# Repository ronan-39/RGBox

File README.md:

# RGBox
 Slim hitbox styled fighting game controller based on the RP2040 microcontroller. Laser cut acyrlic case with 3D printed keycaps for Kailh low profile mechanical switches.

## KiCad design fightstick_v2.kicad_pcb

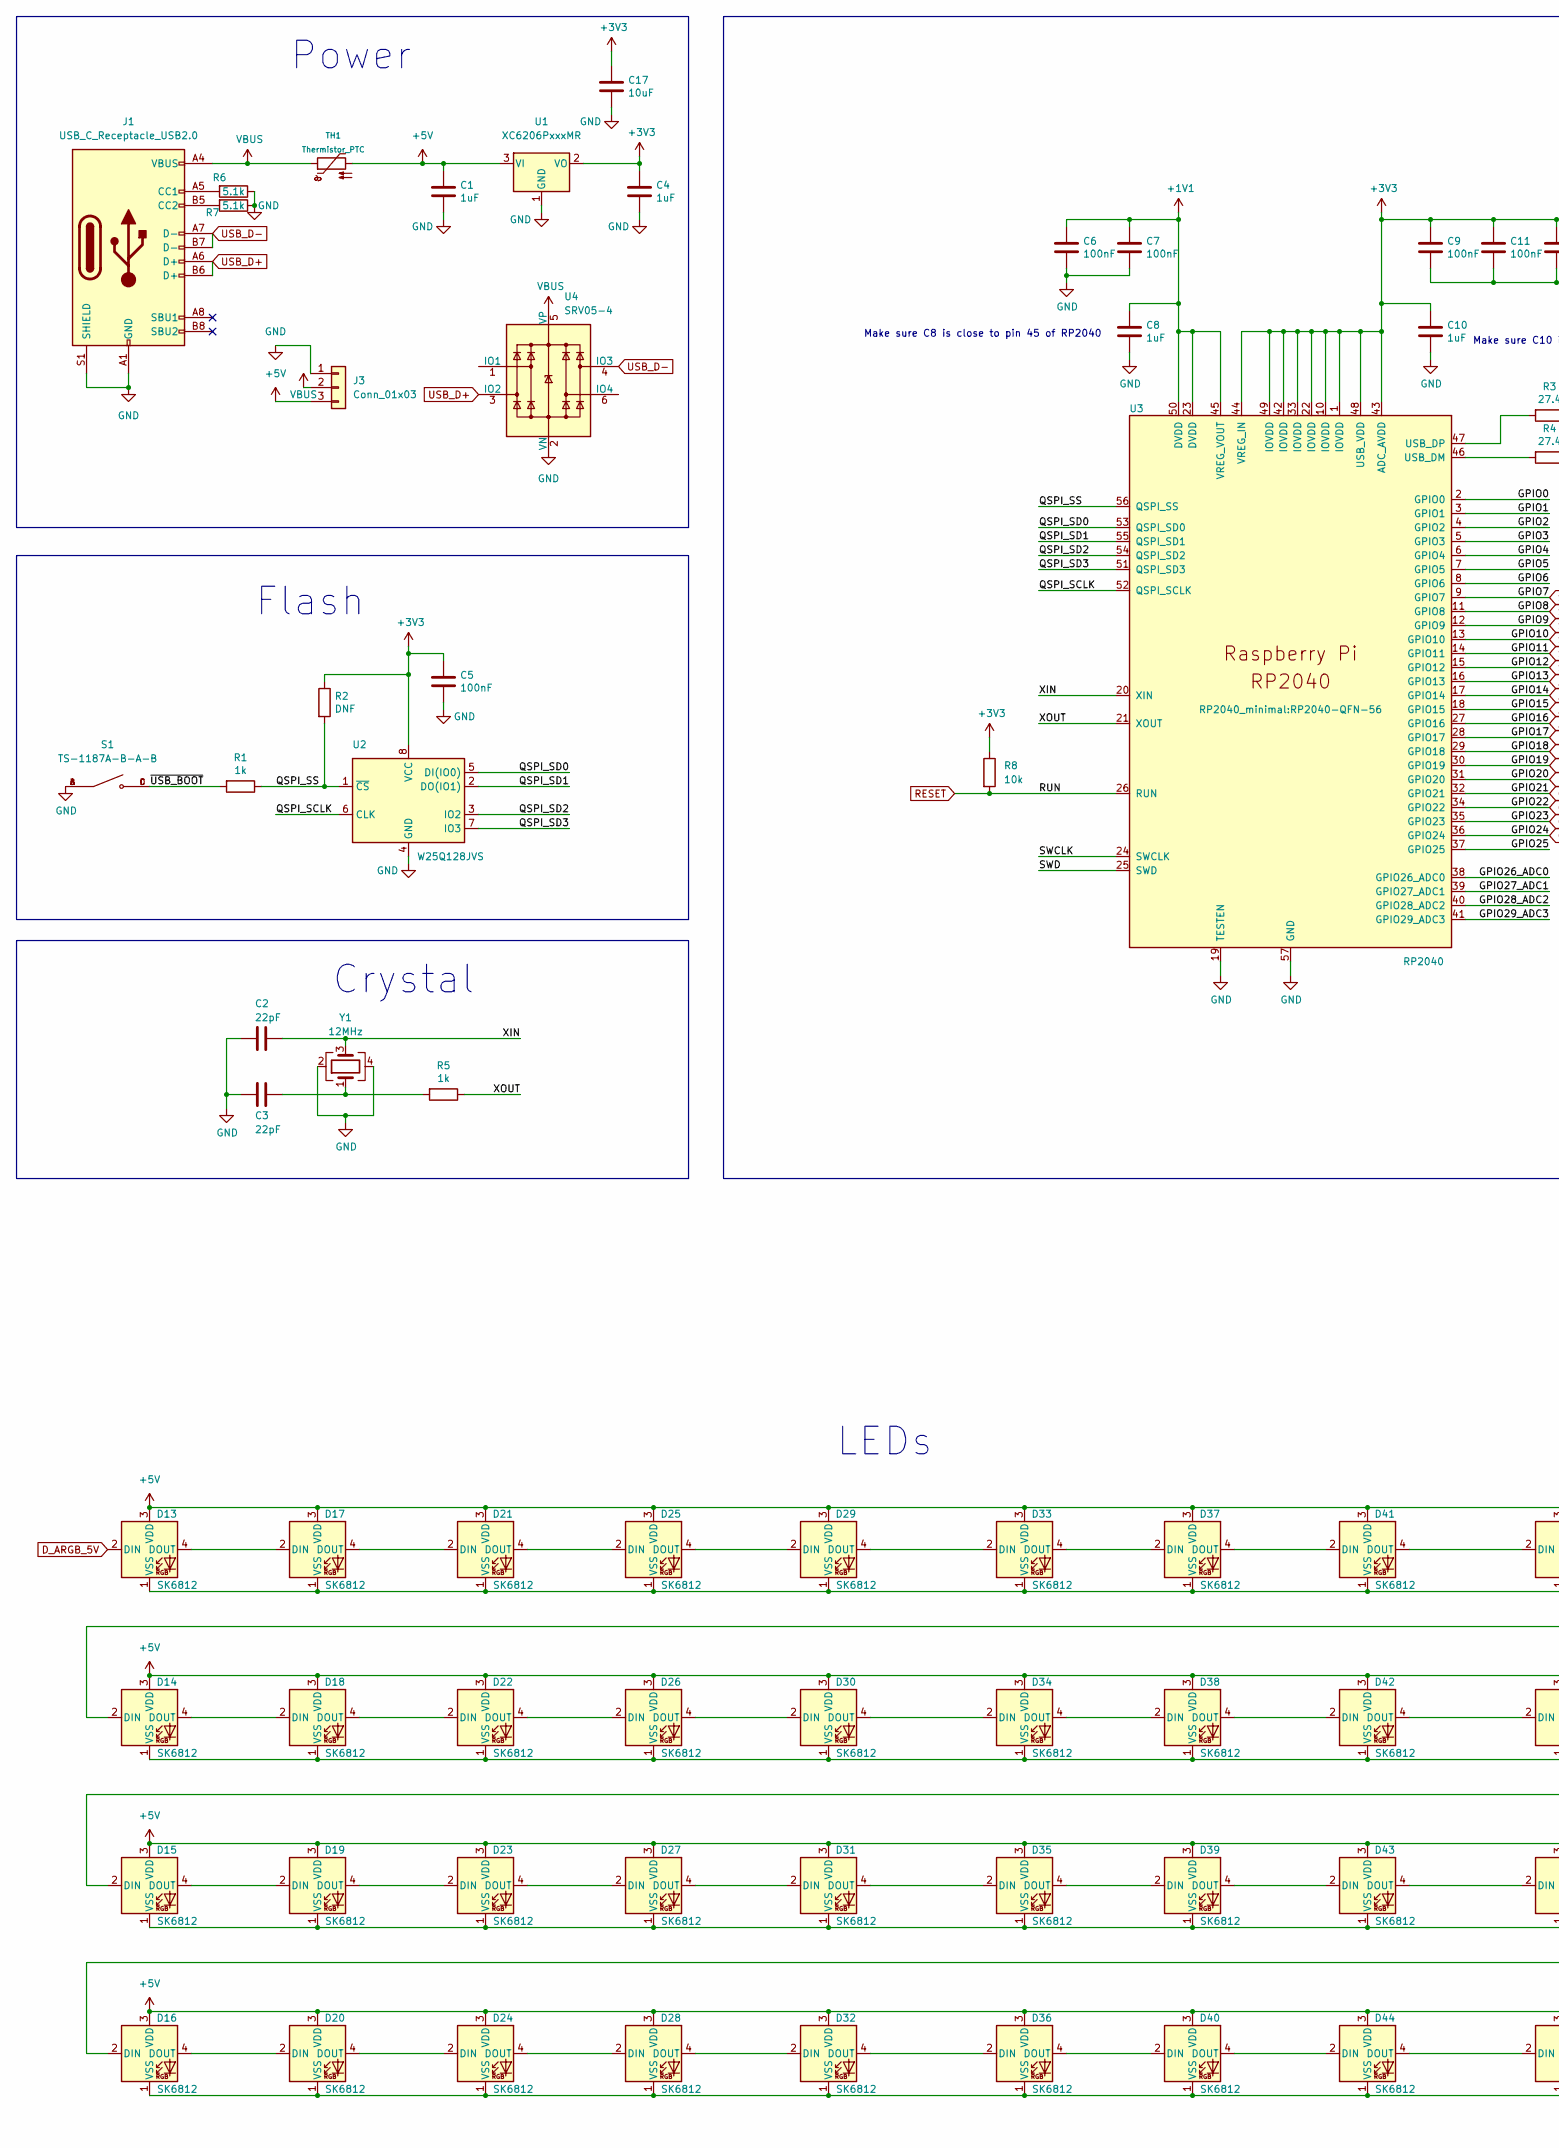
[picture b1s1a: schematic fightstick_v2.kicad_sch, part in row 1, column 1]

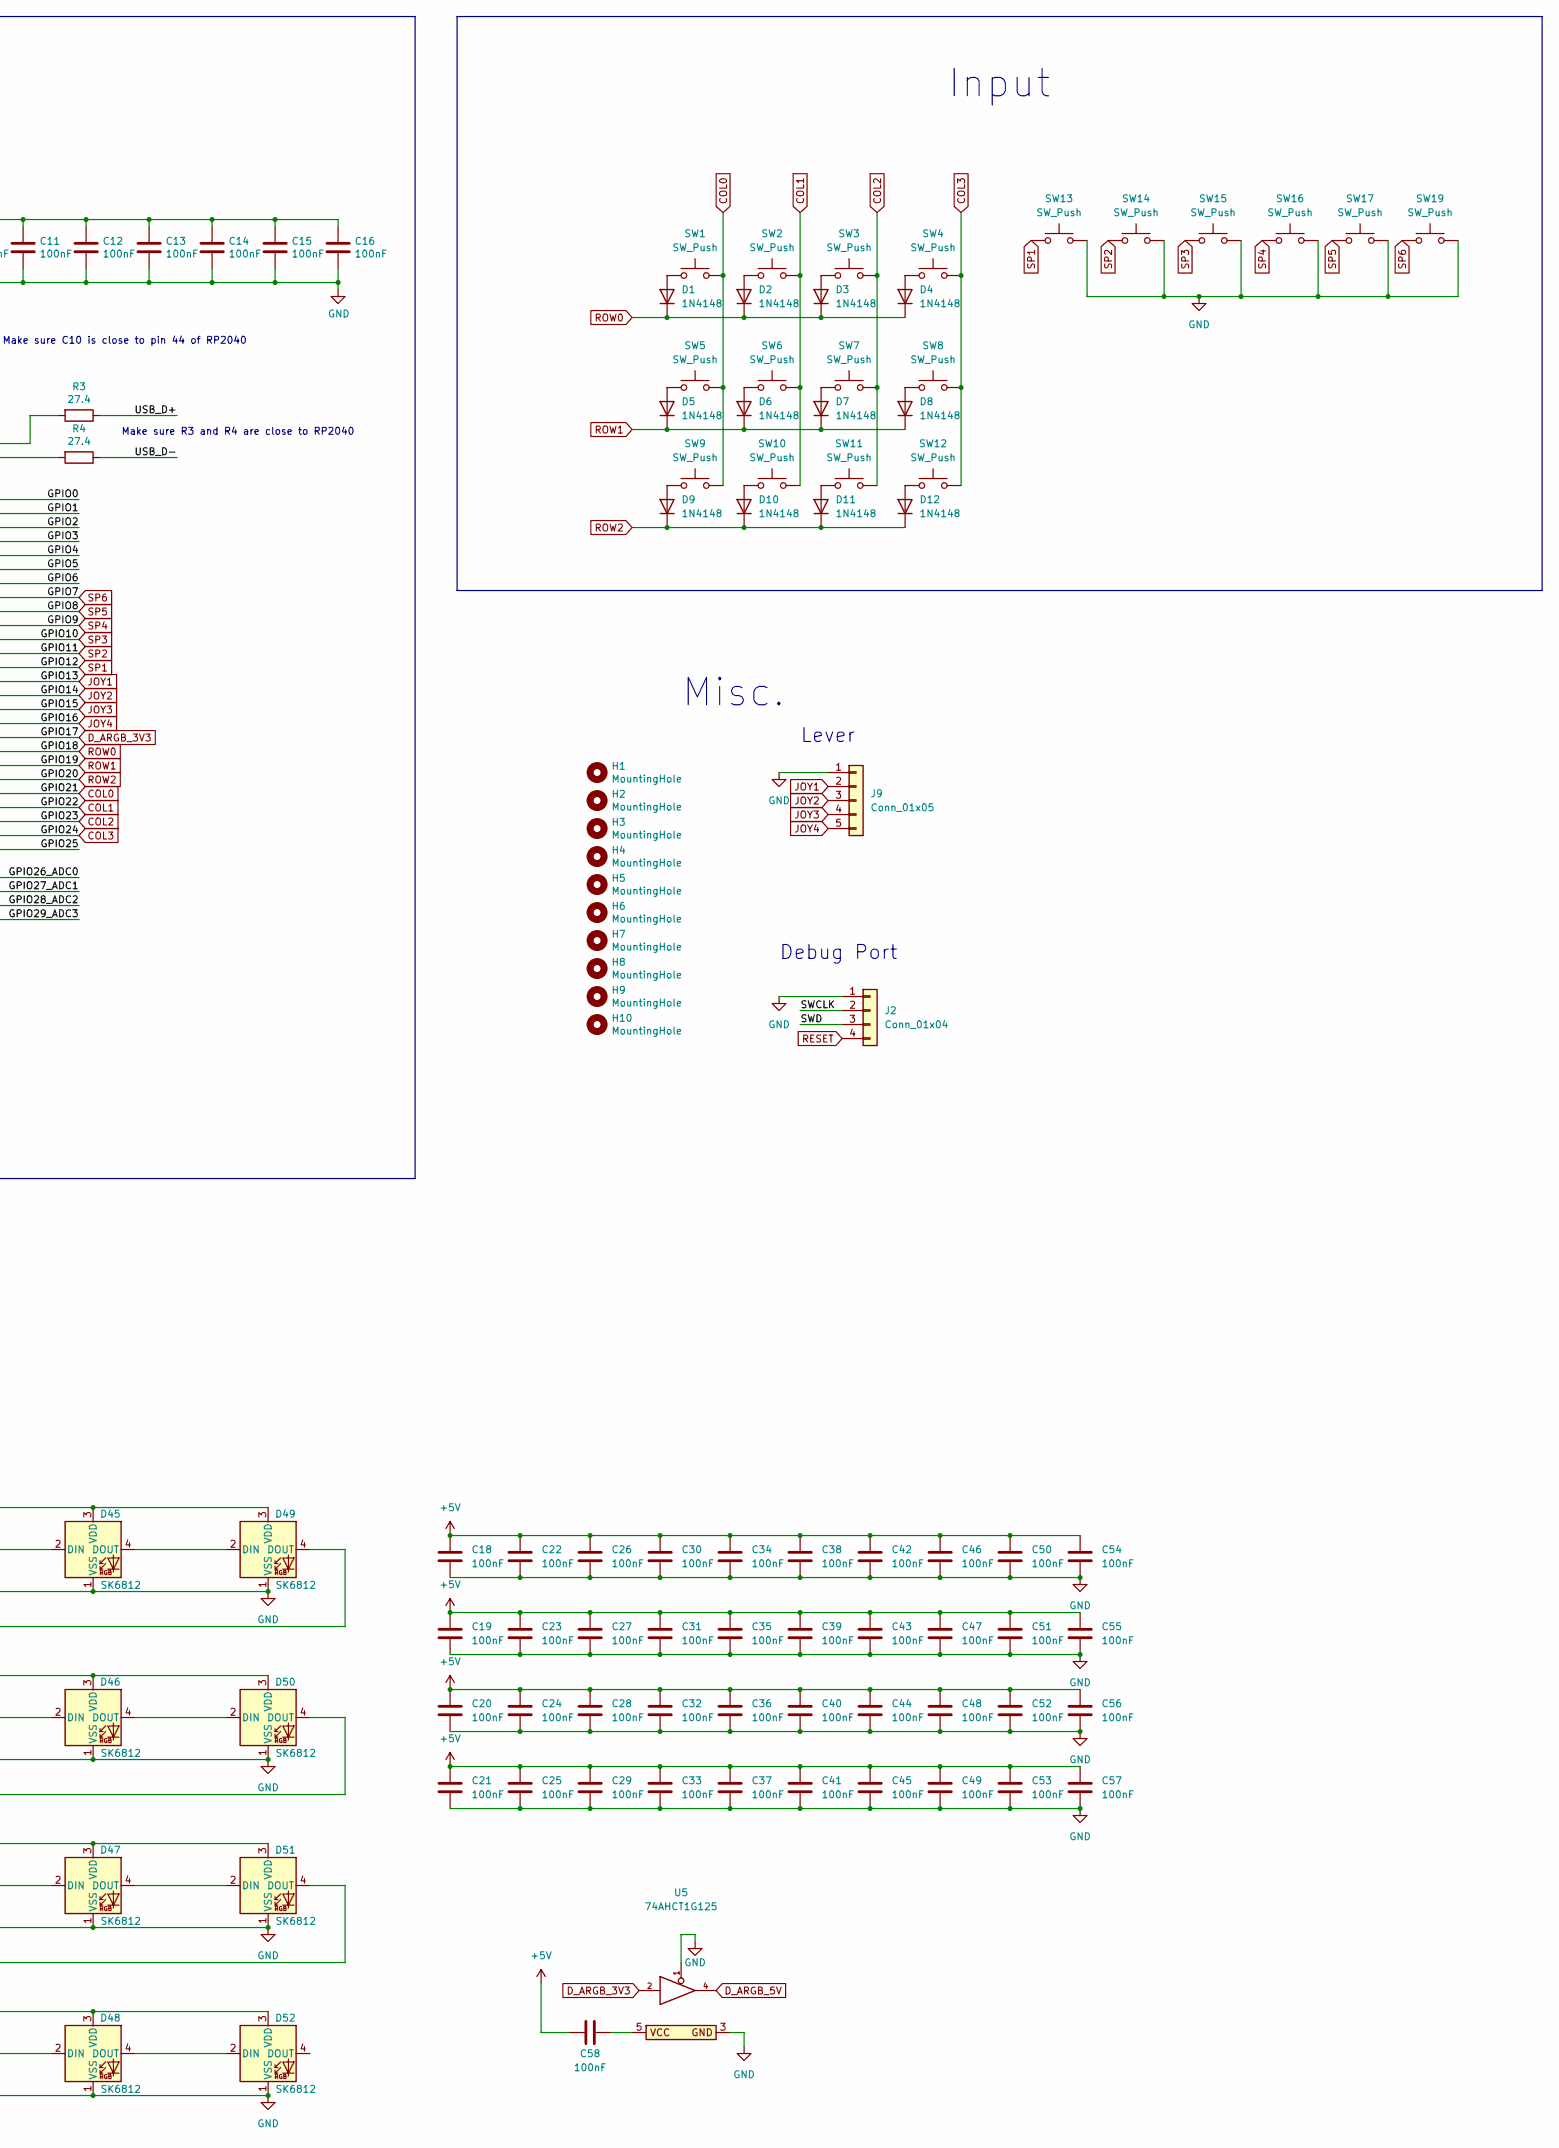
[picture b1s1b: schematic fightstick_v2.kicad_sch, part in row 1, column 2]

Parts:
C1, C4, C8, C10: 1uF; C_0402_1005Metric; LCSC C52923
C2, C3: 22pF; C_0402_1005Metric; LCSC C1555
C5, C6, C7, C9, C11, C12, C13, C14, C15, C16, C18, C19, C20, C21, C22, C23, C24, C25, C26, C27, C28, C29, C30, C31, C32, C33, C34, C35, C36, C37, C38, C39, C40, C41, C42, C43, C44, C45, C46, C47, C48, C49, C50, C51, C52, C53, C54, C55, C56, C57, C58: 100nF; C_0402_1005Metric; LCSC C1525
C17: 10uF; C_0805_2012Metric; LCSC C15850
D1, D2, D3, D4, D5, D6, D7, D8, D9, D10, D11, D12: 1N4148; D_SOD-123; LCSC C81598
D13, D14, D15, D16, D17, D18, D19, D20, D21, D22, D23, D24, D25, D26, D27, D28, D29, D30, D31, D32, D33, D34, D35, D36, D37, D38, D39, D40, D41, D42, D43, D44, D45, D46, D47, D48, D49, D50, D51, D52: SK6812; LED_SK6805_PLCC4_2.4x2.7mm_P1.3mm; LCSC C2909058
H1, H2, H3, H4, H5, H6, H7, H8, H9, H10: MountingHole; MountingHole_2.2mm_M2
J1: USB_C_Receptacle_USB2.0; USB_C_Receptacle_HRO_TYPE-C-31-M-12; LCSC C165948
J2: Conn_01x04; PinHeader_1x04_P2.54mm_Vertical
J3: Conn_01x03; PinHeader_1x03_P2.54mm_Vertical
J9: Conn_01x05; PinHeader_1x05_P1.27mm_Vertical
R1, R5: 1k; C_0402_1005Metric; LCSC C11702
R2: DNF; C_0402_1005Metric
R3, R4: 27.4; C_0603_1608Metric; LCSC C25190
R6, R7: 5.1k; C_0402_1005Metric; LCSC C25905
R8: 10k; C_0402_1005Metric; LCSC C25744
S1: TS-1187A-B-A-B; SW_TS-1187A-B-A-B; PARTREV A0; LCSC C318884
SW1, SW2, SW3, SW4, SW5, SW6, SW7, SW8, SW9, SW10, SW11, SW12: SW_Push; kailh_alternate
SW13, SW14, SW15, SW16, SW17, SW19: SW_Push; SW_BUTT-2-4
TH1: Thermistor_PTC; Fuse_1206_3216Metric; LCSC C70076
U1: XC6206PxxxMR; SOT-23; LCSC C5446
U2: W25Q128JVS; SOIC-8_5.23x5.23mm_P1.27mm; LCSC C97521
U3: RP2040; RP2040-QFN-56; LCSC C2040
U4: SRV05-4; SOT-23-6-routable; LCSC C85364
U5: 74AHCT1G125; SOT-23-5; LCSC C7484
Y1: 12MHz; Crystal_SMD_3225-4Pin_3.2x2.5mm; LCSC C9002

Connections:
+1V1: C6.1, C7.1, C8.1, U3.23 (DVDD), U3.45 (VREG_VOUT), U3.50 (DVDD)
+3V3: C4.1, C5.1, C9.1, C10.1, C11.1, C12.1, C13.1, C14.1, C15.1, C16.1, C17.1, R2.1, R8.1, U1.2 (VO), U2.8 (VCC), U3.1 (IOVDD), U3.10 (IOVDD), U3.22 (IOVDD), U3.33 (IOVDD), U3.42 (IOVDD), U3.43 (ADC_AVDD), U3.44 (VREG_IN), U3.48 (USB_VDD), U3.49 (IOVDD)
+5V: C1.1, C18.1, C19.1, C20.1, C21.1, C22.1, C23.1, C24.1, C25.1, C26.1, C27.1, C28.1, C29.1, C30.1, C31.1, C32.1, C33.1, C34.1, C35.1, C36.1, C37.1, C38.1, C39.1, C40.1, C41.1, C42.1, C43.1, C44.1, C45.1, C46.1, C47.1, C48.1, C49.1, C50.1, C51.1, C52.1, C53.1, C54.1, C55.1, C56.1, C57.1, C58.2, D13.3 (VDD), D14.3 (VDD), D15.3 (VDD), D16.3 (VDD), D17.3 (VDD), D18.3 (VDD), D19.3 (VDD), D20.3 (VDD), D21.3 (VDD), D22.3 (VDD), D23.3 (VDD), D24.3 (VDD), D25.3 (VDD), D26.3 (VDD), D27.3 (VDD), D28.3 (VDD), D29.3 (VDD), D30.3 (VDD), D31.3 (VDD), D32.3 (VDD), D33.3 (VDD), D34.3 (VDD), D35.3 (VDD), D36.3 (VDD), D37.3 (VDD), D38.3 (VDD), D39.3 (VDD), D40.3 (VDD), D41.3 (VDD), D42.3 (VDD), D43.3 (VDD), D44.3 (VDD), D45.3 (VDD), D46.3 (VDD), D47.3 (VDD), D48.3 (VDD), D49.3 (VDD), D50.3 (VDD), D51.3 (VDD), D52.3 (VDD), J3.3, TH1.2, U1.3 (VI)
/GPIO0: U3.2 (GPIO0)
/GPIO1: U3.3 (GPIO1)
/GPIO2: U3.4 (GPIO2)
/GPIO3: U3.5 (GPIO3)
/GPIO4: U3.6 (GPIO4)
/GPIO5: U3.7 (GPIO5)
/GPIO6: U3.8 (GPIO6)
/GPIO25: U3.37 (GPIO25)
/GPIO26_ADC0: U3.38 (GPIO26_ADC0)
/GPIO27_ADC1: U3.39 (GPIO27_ADC1)
/GPIO28_ADC2: U3.40 (GPIO28_ADC2)
/GPIO29_ADC3: U3.41 (GPIO29_ADC3)
/QSPI_SCLK: U2.6 (CLK), U3.52 (QSPI_SCLK)
/QSPI_SD0: U2.5 (DI(IO0)), U3.53 (QSPI_SD0)
/QSPI_SD1: U2.2 (DO(IO1)), U3.55 (QSPI_SD1)
/QSPI_SD2: U2.3 (IO2), U3.54 (QSPI_SD2)
/QSPI_SD3: U2.7 (IO3), U3.51 (QSPI_SD3)
/QSPI_SS: R1.1, R2.2, U2.1 (~CS), U3.56 (QSPI_SS)
/SWCLK: J2.2, U3.24 (SWCLK)
/SWD: J2.3, U3.25 (SWD)
/XIN: C2.1, U3.20 (XIN), Y1.3
/XOUT: R5.1, U3.21 (XOUT)
/~USB_BOOT: R1.2, S1.C, S1.D
COL0: SW1.2, SW5.2, SW9.2, U3.32 (GPIO21)
COL1: SW2.2, SW6.2, SW10.2, U3.34 (GPIO22)
COL2: SW3.2, SW7.2, SW11.2, U3.35 (GPIO23)
COL3: SW4.2, SW8.2, SW12.2, U3.36 (GPIO24)
D_ARGB_3V3: U3.28 (GPIO17), U5.2
D_ARGB_5V: D13.2 (DIN), U5.4
GND: C1.2, C2.2, C3.2, C4.2, C5.2, C6.2, C7.2, C8.2, C9.2, C10.2, C11.2, C12.2, C13.2, C14.2, C15.2, C16.2, C17.2, C18.2, C19.2, C20.2, C21.2, C22.2, C23.2, C24.2, C25.2, C26.2, C27.2, C28.2, C29.2, C30.2, C31.2, C32.2, C33.2, C34.2, C35.2, C36.2, C37.2, C38.2, C39.2, C40.2, C41.2, C42.2, C43.2, C44.2, C45.2, C46.2, C47.2, C48.2, C49.2, C50.2, C51.2, C52.2, C53.2, C54.2, C55.2, C56.2, C57.2, D13.1 (VSS), D14.1 (VSS), D15.1 (VSS), D16.1 (VSS), D17.1 (VSS), D18.1 (VSS), D19.1 (VSS), D20.1 (VSS), D21.1 (VSS), D22.1 (VSS), D23.1 (VSS), D24.1 (VSS), D25.1 (VSS), D26.1 (VSS), D27.1 (VSS), D28.1 (VSS), D29.1 (VSS), D30.1 (VSS), D31.1 (VSS), D32.1 (VSS), D33.1 (VSS), D34.1 (VSS), D35.1 (VSS), D36.1 (VSS), D37.1 (VSS), D38.1 (VSS), D39.1 (VSS), D40.1 (VSS), D41.1 (VSS), D42.1 (VSS), D43.1 (VSS), D44.1 (VSS), D45.1 (VSS), D46.1 (VSS), D47.1 (VSS), D48.1 (VSS), D49.1 (VSS), D50.1 (VSS), D51.1 (VSS), D52.1 (VSS), J1.A1 (GND), J1.A12 (GND), J1.B1 (GND), J1.B12 (GND), J1.S1 (SHIELD), J2.1, J3.1, J9.1, R6.1, R7.1, S1.A, S1.B, SW13.2, SW14.2, SW15.2, SW16.2, SW17.2, SW19.2, U1.1 (GND), U2.4 (GND), U3.19 (TESTEN), U3.57 (GND), U4.2 (VN), U5.1, U5.3 (GND), Y1.2, Y1.4
JOY1: J9.2, U3.16 (GPIO13)
JOY2: J9.3, U3.17 (GPIO14)
JOY3: J9.4, U3.18 (GPIO15)
JOY4: J9.5, U3.27 (GPIO16)
unnamed: C3.1, R5.2, Y1.1
unnamed: C58.1, U5.5
unnamed: D1.2 (A), SW1.1
unnamed: D2.2 (A), SW2.1
unnamed: D3.2 (A), SW3.1
unnamed: D4.2 (A), SW4.1
unnamed: D5.2 (A), SW5.1
unnamed: D6.2 (A), SW6.1
unnamed: D7.2 (A), SW7.1
unnamed: D8.2 (A), SW8.1
unnamed: D9.2 (A), SW9.1
unnamed: D10.2 (A), SW10.1
unnamed: D11.2 (A), SW11.1
unnamed: D12.2 (A), SW12.1
unnamed: D13.4 (DOUT), D17.2 (DIN)
unnamed: D14.2 (DIN), D49.4 (DOUT)
unnamed: D14.4 (DOUT), D18.2 (DIN)
unnamed: D15.2 (DIN), D50.4 (DOUT)
unnamed: D15.4 (DOUT), D19.2 (DIN)
unnamed: D16.2 (DIN), D51.4 (DOUT)
unnamed: D16.4 (DOUT), D20.2 (DIN)
unnamed: D17.4 (DOUT), D21.2 (DIN)
unnamed: D18.4 (DOUT), D22.2 (DIN)
unnamed: D19.4 (DOUT), D23.2 (DIN)
unnamed: D20.4 (DOUT), D24.2 (DIN)
unnamed: D21.4 (DOUT), D25.2 (DIN)
unnamed: D22.4 (DOUT), D26.2 (DIN)
unnamed: D23.4 (DOUT), D27.2 (DIN)
unnamed: D24.4 (DOUT), D28.2 (DIN)
unnamed: D25.4 (DOUT), D29.2 (DIN)
unnamed: D26.4 (DOUT), D30.2 (DIN)
unnamed: D27.4 (DOUT), D31.2 (DIN)
unnamed: D28.4 (DOUT), D32.2 (DIN)
unnamed: D29.4 (DOUT), D33.2 (DIN)
unnamed: D30.4 (DOUT), D34.2 (DIN)
unnamed: D31.4 (DOUT), D35.2 (DIN)
unnamed: D32.4 (DOUT), D36.2 (DIN)
unnamed: D33.4 (DOUT), D37.2 (DIN)
unnamed: D34.4 (DOUT), D38.2 (DIN)
unnamed: D35.4 (DOUT), D39.2 (DIN)
unnamed: D36.4 (DOUT), D40.2 (DIN)
unnamed: D37.4 (DOUT), D41.2 (DIN)
unnamed: D38.4 (DOUT), D42.2 (DIN)
unnamed: D39.4 (DOUT), D43.2 (DIN)
unnamed: D40.4 (DOUT), D44.2 (DIN)
unnamed: D41.4 (DOUT), D45.2 (DIN)
unnamed: D42.4 (DOUT), D46.2 (DIN)
unnamed: D43.4 (DOUT), D47.2 (DIN)
unnamed: D44.4 (DOUT), D48.2 (DIN)
unnamed: D45.4 (DOUT), D49.2 (DIN)
unnamed: D46.4 (DOUT), D50.2 (DIN)
unnamed: D47.4 (DOUT), D51.2 (DIN)
unnamed: D48.4 (DOUT), D52.2 (DIN)
unnamed: J1.A5 (CC1), R6.2
unnamed: J1.B5 (CC2), R7.2
unnamed: R3.2, U3.47 (USB_DP)
unnamed: R4.2, U3.46 (USB_DM)
RESET: J2.4, R8.2, U3.26 (RUN)
ROW0: D1.1 (K), D2.1 (K), D3.1 (K), D4.1 (K), U3.29 (GPIO18)
ROW1: D5.1 (K), D6.1 (K), D7.1 (K), D8.1 (K), U3.30 (GPIO19)
ROW2: D9.1 (K), D10.1 (K), D11.1 (K), D12.1 (K), U3.31 (GPIO20)
SP1: SW13.1, U3.15 (GPIO12)
SP2: SW14.1, U3.14 (GPIO11)
SP3: SW15.1, U3.13 (GPIO10)
SP4: SW16.1, U3.12 (GPIO9)
SP5: SW17.1, U3.11 (GPIO8)
SP6: SW19.1, U3.9 (GPIO7)
USB_D+: J1.A6 (D+), J1.B6 (D+), R3.1, U4.3 (IO2)
USB_D-: J1.A7 (D-), J1.B7 (D-), R4.1, U4.4 (IO3)
VBUS: J1.A4 (VBUS), J1.A9 (VBUS), J1.B4 (VBUS), J1.B9 (VBUS), J3.2, TH1.1, U4.5 (VP)

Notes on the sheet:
Misc.
Crystal
Make sure C8 is close to pin 45 of RP2040
Make sure R3 and R4 are close to RP2040
Flash
Debug Port
Make sure C10 is close to pin 44 of RP2040
LEDs
Lever
Power
Input

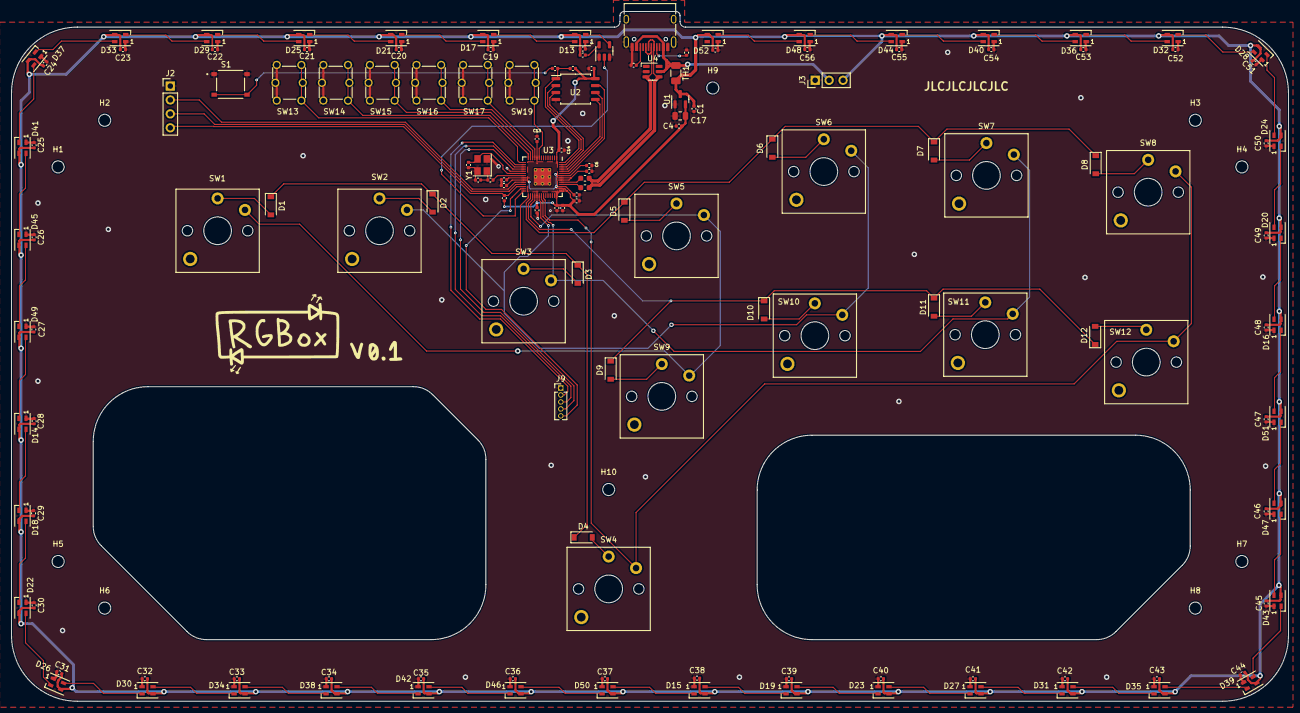
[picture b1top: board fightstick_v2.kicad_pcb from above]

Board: 2 copper layers, 233.0 x 125.9 mm, 158 parts (0 on the bottom side), 95 nets.

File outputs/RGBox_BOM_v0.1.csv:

"Id";"Designator";"Package";"Quantity";"Designation";"Supplier and ref";
1;"S1";"SW_TS-1187A-B-A-B";1;"TS-1187A-B-A-B";;;
2;"D2,D9,D12,D3,D4,D1,D5,D7,D8,D10,D6,D11";"D_SOD-123";12;"1N4148";;;
3;"J2";"PinHeader_1x04_P2.54mm_Vertical";1;"Conn_01x04";;;
4;"C24,C40,C16,C22,C13,C39,C49,C21,C55,C34,C38,C52,C32,C26,C50,C11,C45,C18,C27,C7,C19,C33,C42,C57,C58,C53,C30,C35,C44,C37,C14,C6,C43,C23,C54,C31,C56,C41,C48,C36,C20,C46,C25,C12,C47,C28,C51,C5,C29,C9,C15";"C_0402_1005Metric";51;"100nF";;;
5;"H7,H8,H2,H4,H9,H3,H10,H6,H1,H5";"MountingHole_2.2mm_M2";10;"MountingHole";;;
6;"D21,D23,D22,D17,D29,D24,D18,D41,D51,D20,D45,D14,D44,D40,D39,D19,D15,D28,D52,D46,D36,D50,D49,D38,D37,D33,D43,D30,D16,D26,D34,D47,D13,D35,D42,D48,D31,D25,D27,D32";"LED_WS2812-2020";40;"WS2812C-2020";;;
7;"C3,C2";"C_0402_1005Metric";2;"22pF";;;
8;"SW17,SW14,SW15,SW16,SW19,SW13";"SW_BUTT-2-4";6;"SW_Push";;;
9;"R4,R3";"C_0603_1608Metric";2;"27.4";;;
10;"J3";"PinHeader_1x03_P2.54mm_Vertical";1;"Conn_01x03";;;
11;"C8,C1,C10,C4";"C_0402_1005Metric";4;"1uF";;;
12;"R6,R7";"C_0402_1005Metric";2;"5.1k";;;
13;"U2";"SOIC-8_5.23x5.23mm_P1.27mm";1;"W25Q128JVS";;;
14;"R2";"C_0402_1005Metric";1;"DNF";;;
15;"SW6,SW8,SW7,SW1,SW11,SW2,SW9,SW3,SW5,SW4,SW10,SW12";"kailh_alternate";12;"SW_Push";;;
16;"R5,R1";"C_0402_1005Metric";2;"1k";;;
17;"U3";"RP2040-QFN-56";1;"RP2040";;;
18;"U4";"SOT-23-6-routable";1;"SRV05-4";;;
19;"C17";"C_0402_1005Metric";1;"10uF";;;
20;"U1";"SOT-23";1;"XC6206PxxxMR";;;
21;"U5";"SOT-23-5";1;"74AHCT1G125";;;
22;"J9";"PinHeader_1x05_P1.27mm_Vertical";1;"Conn_01x05";;;
23;"TH1";"Fuse_1206_3216Metric";1;"Thermistor_PTC";;;
24;"J1";"USB_C_Receptacle_HRO_TYPE-C-31-M-12";1;"USB_C_Receptacle_USB2.0";;;
25;"Y1";"Crystal_SMD_3225-4Pin_3.2x2.5mm";1;"12MHz";;;
26;"R8";"C_0402_1005Metric";1;"10k";;;

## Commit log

2023-02-26 Fixed Repo
2023-02-26 finished routing and mostly clear DRC
2023-02-27 fixed everything i can tell is wrong
2023-02-27 presentable
2023-02-27 tried creating a bom
2023-02-28 about to try to reroute things
2023-02-28 v0.1, shipping this
2023-03-01 replaced leds with sk6812-ec20s
2023-03-01 last update for now on sk6812 ver
    these are the files im submitting to jlc. im thinking about making a version with dumb led's which would save me about $10 minimum but that will go on a different branch
2023-06-17 currrent working hid descriptor
2023-11-07 added screenshot
2024-01-25 added picture
